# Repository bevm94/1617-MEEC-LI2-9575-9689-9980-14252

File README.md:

# 1617-MEEC-LI2-9575-9689-9980-14252
Trabalho de Laboratórios Integrados II

O presente trabalho prático visa a implementação de um sistema de reconhecimento facial que integra dois blocos principais: um baseado em PC que é responsável pelo processamento e análise de imagem e o outro é baseado em sistemas embebidos, que gere a comunicação através do protocolo de comunicação CAN dos dados analisados pelo módulo baseado em PC.
O sistema embebido foi composto pela componente de Hardware e Software. A componente de Hardware foi implementada utilizando o EAGLE onde foram implementadas duas placas: uma placa para o Master e outra para o Slave. Para a criação das PCB foram seguidas as regras disponibilizadas pelo docente e posteriormente foram criados os ficheiros GERBER essenciais para a confeção das placas. Uma vez que as PCB's não ficaram prontas em tempo útil, foi necessária a montagem em Breadboard onde foi simulado o comportamento do sistema pela utilização de LEDs e Botões.
A parte de Software que tratou do reconhecimento facial foi efetuada em Visual Studio, que também serviu de base para a criação da interface do bloco baseado em PC.

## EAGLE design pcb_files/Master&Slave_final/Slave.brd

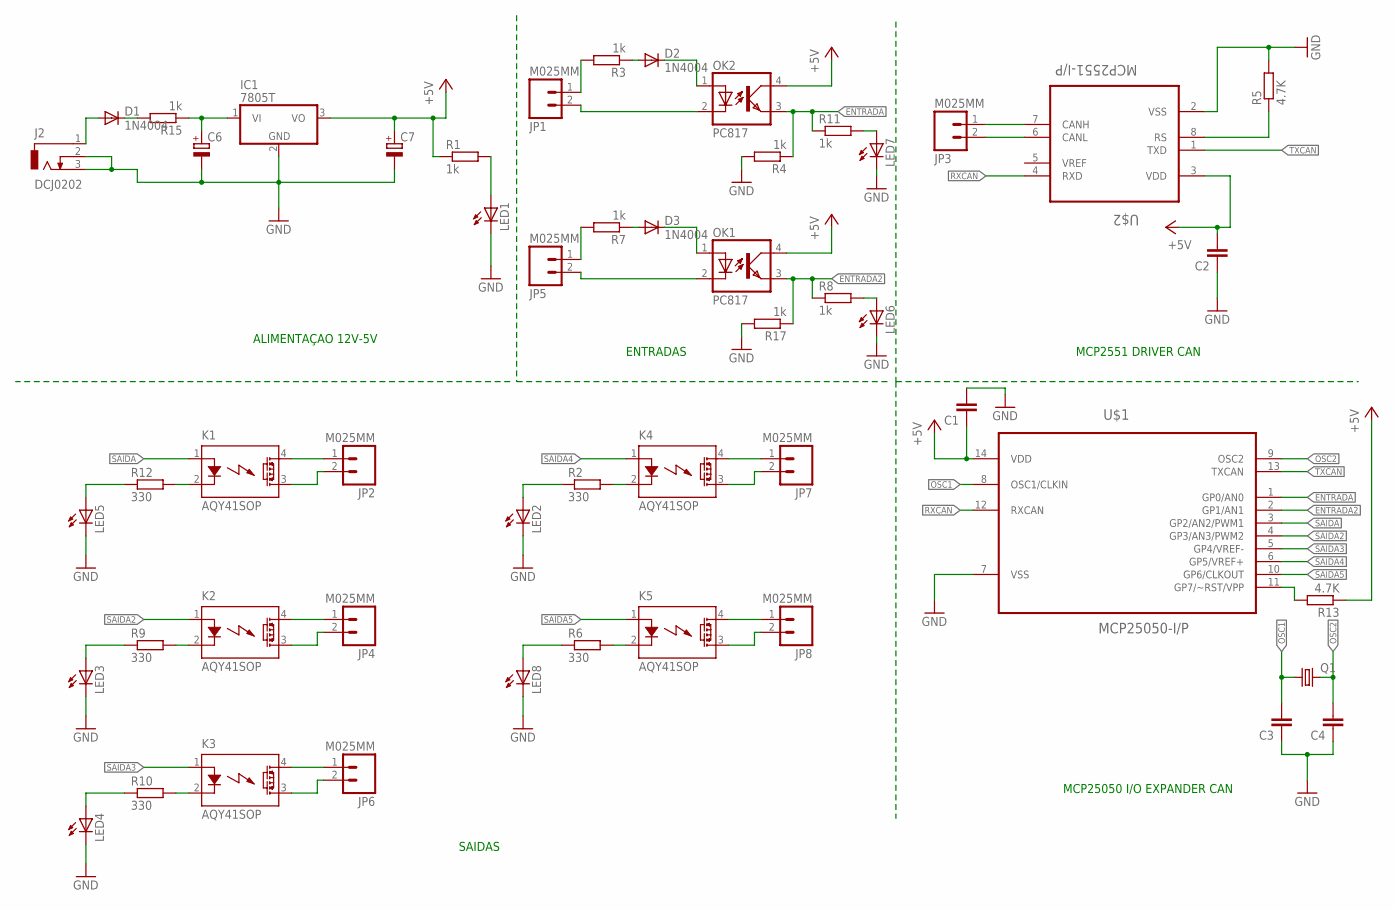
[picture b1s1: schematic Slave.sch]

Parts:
C1, C2: C-EU025-025X050; C025-025X050
C3, C4: CAP_; AXIAL-5MM
C6, C7: CPOL-EUE2.5-6; E2,5-6
D1, D2, D3: 1N4004; DO41-10
IC1: 7805T; TO220H
J2: DCJ0202
JP1, JP2, JP3, JP4, JP5, JP6, JP7, JP8: M025MM; SCREWTERMINAL-5MM-2
K1, K2, K3, K4, K5: AQY41SOP; SOP04
LED1, LED2, LED3, LED4, LED5, LED6, LED7, LED8: LED_ELD260; LED_LD260
OK1, OK2: PC817; DIL04
Q1: CRYTALHC49S; HC49/S
R1, R3, R4, R7, R8, R11, R15, R17: 1k; 0204/7
R2, R6, R9, R10, R12: 330; 0204/7
R5, R13: 4.7K; 0204/7
U$1: MCP25050-I/P; DIP254P762X432-14
U$2: MCP2551-I/P; DIP254P762X432-8

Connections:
+5V: C1.1, C2.2, C7.+, IC1.3 (VO), OK1.4 (COL), OK2.4 (COL), R1.1, R13.1, U$1.14 (VDD), U$2.3 (VDD)
ENTRADA: OK2.3 (EMIT), R4.1, R11.1, U$1.1 (GP0/AN0)
ENTRADA2: OK1.3 (EMIT), R8.1, R17.1, U$1.2 (GP1/AN1)
GND: C1.2, C2.1, C3.P$1 (1), C4.P$1 (1), C6.-, C7.-, IC1.2 (GND), J2.2, J2.3, LED1.K (C), LED2.K (C), LED3.K (C), LED4.K (C), LED5.K (C), LED6.K (C), LED7.K (C), LED8.K (C), R4.2, R5.2, R17.2, U$1.7 (VSS), U$2.2 (VSS)
unnamed: R5.1, U$2.8 (RS)
unnamed: JP2.2, K1.3 (DS2)
unnamed: JP2.1, K1.4 (DS1)
unnamed: K2.2 (K), R9.2
unnamed: JP1.1, R3.2
unnamed: LED1.A, R1.2
unnamed: R13.2, U$1.11 (GP7/~RST/VPP)
unnamed: D2.A, R3.1
unnamed: D2.C, OK2.1 (A)
unnamed: JP1.2, OK2.2 (C)
unnamed: D1.A, J2.1
unnamed: JP5.1, R7.2
unnamed: D1.C, R15.2
unnamed: D3.A, R7.1
unnamed: D3.C, OK1.1 (A)
unnamed: JP3.1, U$2.7 (CANH)
unnamed: LED3.A, R9.1
unnamed: JP4.2, K2.3 (DS2)
unnamed: JP4.1, K2.4 (DS1)
unnamed: K1.2 (K), R12.2
unnamed: LED5.A, R12.1
unnamed: K3.2 (K), R10.2
unnamed: LED4.A, R10.1
unnamed: JP6.2, K3.3 (DS2)
unnamed: JP6.1, K3.4 (DS1)
unnamed: C6.+, IC1.1 (VI), R15.1
unnamed: JP3.2, U$2.6 (CANL)
unnamed: LED6.A, R8.2
unnamed: LED7.A, R11.2
unnamed: K4.2 (K), R2.2
unnamed: JP5.2, OK1.2 (C)
unnamed: LED2.A, R2.1
unnamed: JP7.2, K4.3 (DS2)
unnamed: JP7.1, K4.4 (DS1)
unnamed: K5.2 (K), R6.2
unnamed: LED8.A, R6.1
unnamed: JP8.2, K5.3 (DS2)
unnamed: JP8.1, K5.4 (DS1)
OSC1: C3.P$2 (2), Q1.1, U$1.8 (OSC1/CLKIN)
OSC2: C4.P$2 (2), Q1.2, U$1.9 (OSC2)
RXCAN: U$1.12 (RXCAN), U$2.4 (RXD)
SAIDA: K1.1 (A), U$1.3 (GP2/AN2/PWM1)
SAIDA2: K2.1 (A), U$1.4 (GP3/AN3/PWM2)
SAIDA3: K3.1 (A), U$1.5 (GP4/VREF-)
SAIDA4: K4.1 (A), U$1.6 (GP5/VREF+)
SAIDA5: K5.1 (A), U$1.10 (GP6/CLKOUT)
TXCAN: U$1.13 (TXCAN), U$2.1 (TXD)

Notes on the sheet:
MCP2551 DRIVER CAN
MCP25050 I/O EXPANDER CAN
ALIMENTAÇAO 12V-5V
SAIDAS
ENTRADAS

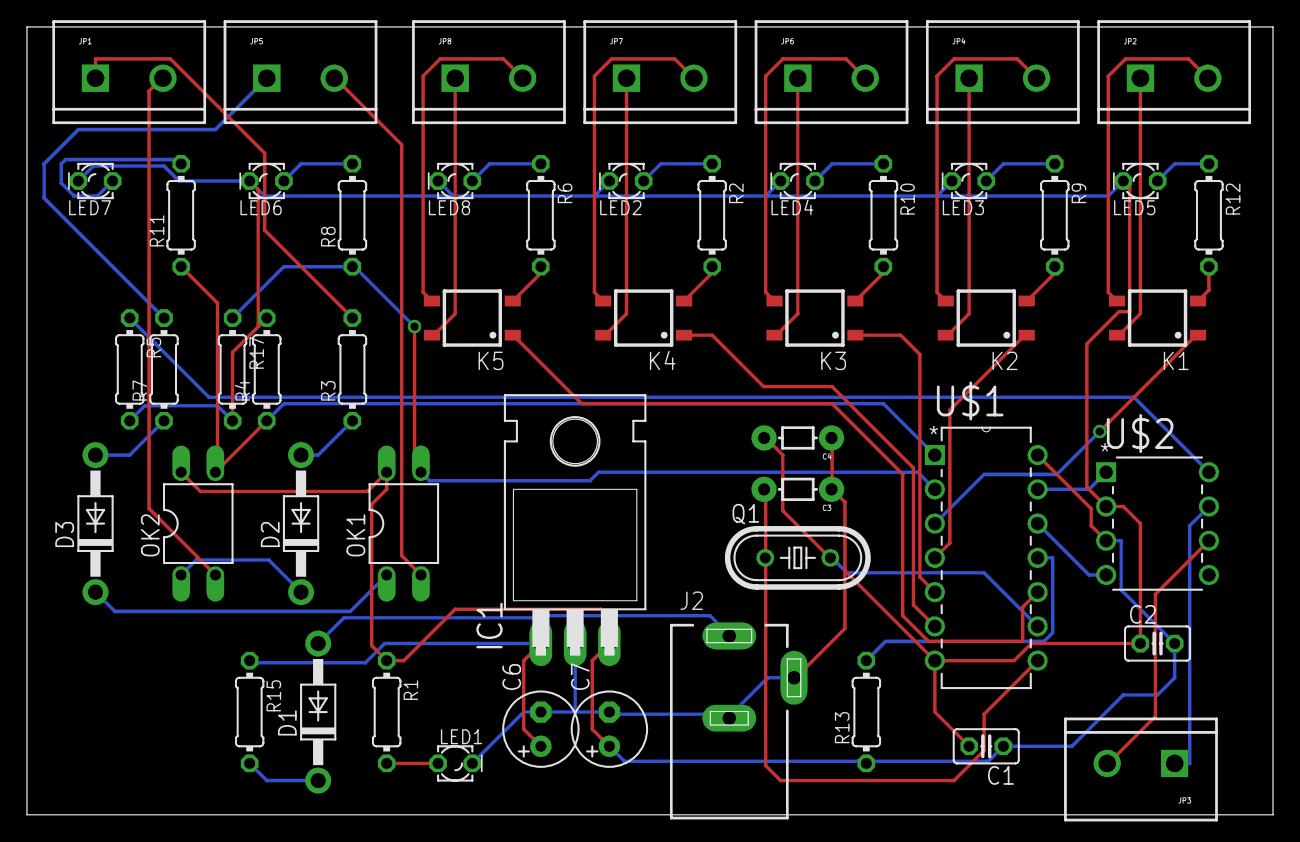
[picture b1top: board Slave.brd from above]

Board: 2 copper layers, 92.4 x 58.4 mm, 52 parts (0 on the bottom side), 51 nets.

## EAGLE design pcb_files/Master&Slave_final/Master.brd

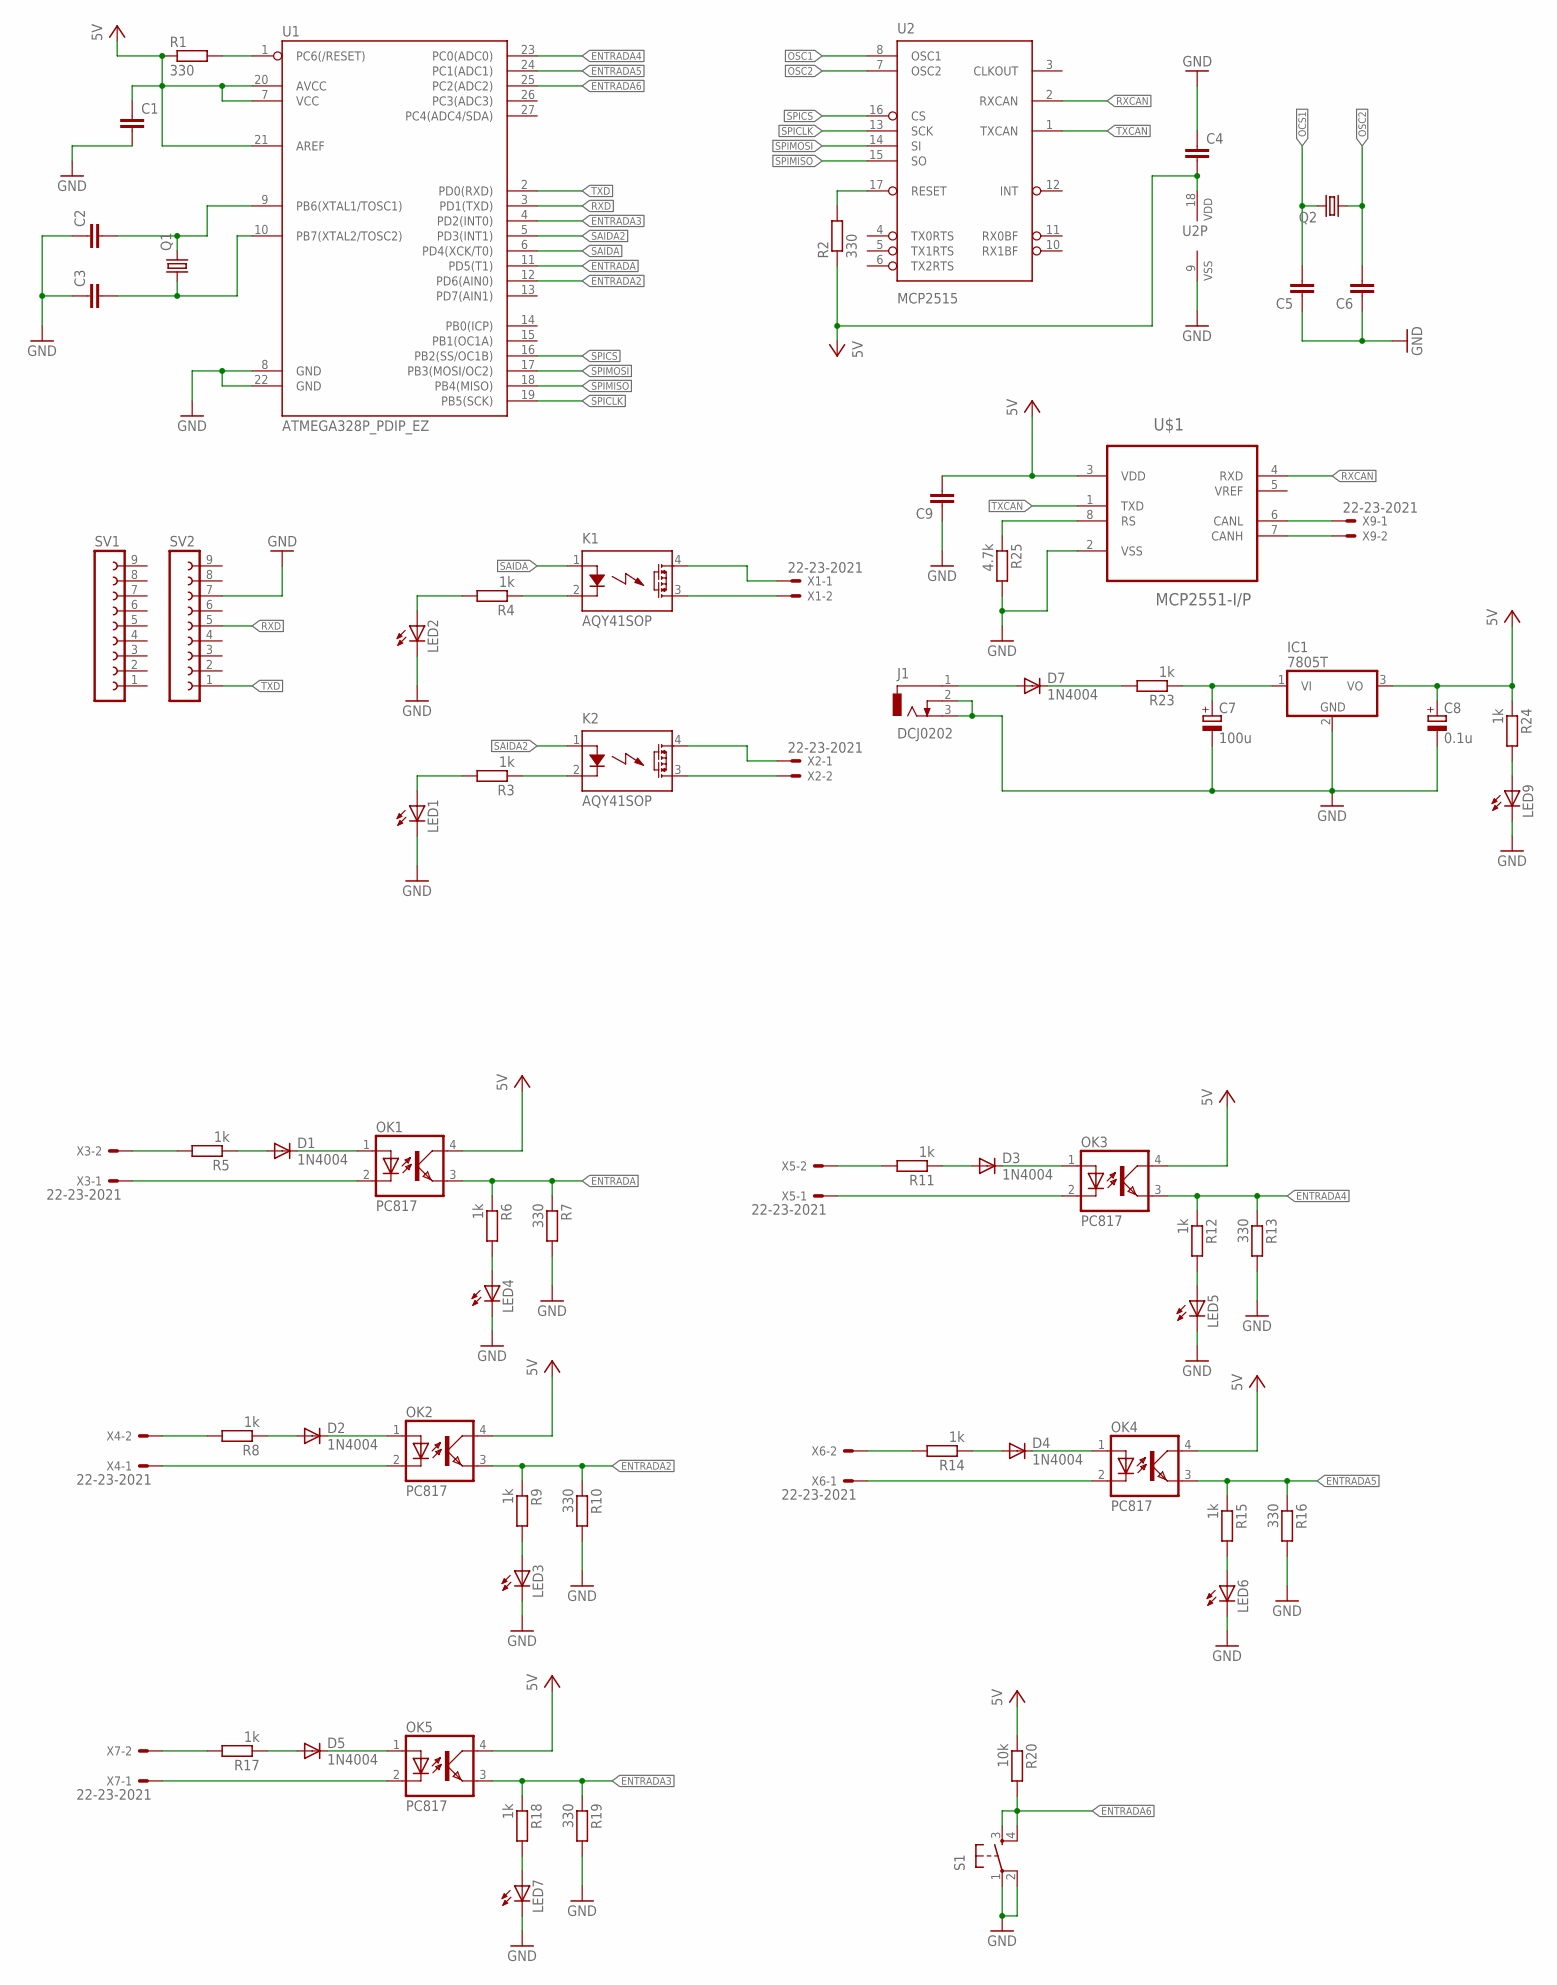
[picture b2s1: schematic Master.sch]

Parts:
C1, C2, C3, C4, C5, C6, C9: C2,5-3; C2.5-3
C7: 100u; E2,5-6
C8: 0.1u; E2,5-6
D1, D2, D3, D4, D5, D7: 1N4004; DO41-10
IC1: 7805T; TO220H
J1: DCJ0202
K1, K2: AQY41SOP; SOP04
LED1, LED2, LED3, LED4, LED5, LED6, LED7, LED9: LED_ELD260; LED_LD260
OK1, OK2, OK3, OK4, OK5: PC817; DIL04
Q1, Q2: CRYSTALHC49U70; HC49U70
R1, R2, R7, R10, R13, R16, R19: 330; 0204/5
R3, R4, R5, R6, R8, R9, R11, R12, R14, R15, R17, R18, R23, R24: 1k; 0204/5
R20: 10k; 0204/5
R25: 4.7k; 0204/5
S1: TAC_SWITCHPTH; TACTILE-PTH
SV1, SV2: FE09-1; FE09
U1: ATMEGA328P_PDIP_EZ; DIP28-SIMON-KIT
U2: MCP2515; DIP18
U$1: MCP2551-I/P; DIP254P762X432-8
X1, X2, X3, X4, X5, X6, X7, X9: 22-23-2021

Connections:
ENTRADA: OK1.3 (EMIT), R6.1, R7.1, U1.11 (PD5(T1))
ENTRADA2: OK2.3 (EMIT), R9.1, R10.1, U1.12 (PD6(AIN0))
ENTRADA3: OK5.3 (EMIT), R18.1, R19.1, U1.4 (PD2(INT0))
ENTRADA4: OK3.3 (EMIT), R12.1, R13.1, U1.23 (PC0(ADC0))
ENTRADA5: OK4.3 (EMIT), R15.1, R16.1, U1.24 (PC1(ADC1))
ENTRADA6: R20.2, S1.3, S1.4, U1.25 (PC2(ADC2))
GND: C1.2, C2.1, C3.1, C4.1, C5.1, C6.1, C7.-, C8.-, C9.1, IC1.2 (GND), J1.2, J1.3, LED1.K (C), LED2.K (C), LED3.K (C), LED4.K (C), LED5.K (C), LED6.K (C), LED7.K (C), LED9.K (C), R7.2, R10.2, R13.2, R16.2, R19.2, R25.2, S1.1, S1.2, SV2.7, U1.8 (GND), U1.22 (GND), U2.9 (VSS), U$1.2 (VSS)
unnamed: R1.2, U1.1 (PC6(/RESET))
unnamed: C2.2, Q1.2, U1.9 (PB6(XTAL1/TOSC1))
unnamed: C3.2, Q1.1, U1.10 (PB7(XTAL2/TOSC2))
unnamed: R2.2, U2.17 (RESET)
unnamed: LED1.A, R3.2
unnamed: K2.2 (K), R3.1
unnamed: K1.2 (K), R4.1
unnamed: LED2.A, R4.2
unnamed: K1.3 (DS2), X1.2
unnamed: K1.4 (DS1), X1.1
unnamed: K2.4 (DS1), X2.1
unnamed: K2.3 (DS2), X2.2
unnamed: R5.2, X3.2
unnamed: D1.A, R5.1
unnamed: D1.C, OK1.1 (A)
unnamed: OK1.2 (C), X3.1
unnamed: R8.2, X4.2
unnamed: LED4.A, R6.2
unnamed: D2.A, R8.1
unnamed: D2.C, OK2.1 (A)
unnamed: OK2.2 (C), X4.1
unnamed: LED3.A, R9.2
unnamed: R11.2, X5.2
unnamed: D3.A, R11.1
unnamed: D3.C, OK3.1 (A)
unnamed: OK3.2 (C), X5.1
unnamed: LED5.A, R12.2
unnamed: R14.2, X6.2
unnamed: D4.A, R14.1
unnamed: D4.C, OK4.1 (A)
unnamed: OK4.2 (C), X6.1
unnamed: LED6.A, R15.2
unnamed: R17.2, X7.2
unnamed: D5.A, R17.1
unnamed: D5.C, OK5.1 (A)
unnamed: OK5.2 (C), X7.1
unnamed: LED7.A, R18.2
unnamed: D7.A, J1.1
unnamed: D7.C, R23.2
unnamed: C7.+, IC1.1 (VI), R23.1
unnamed: U$1.6 (CANL), X9.1
unnamed: U$1.7 (CANH), X9.2
unnamed: LED9.A, R24.2
unnamed: R25.1, U$1.8 (RS)
OCS1: C5.2, Q2.2
OSC1: U2.8 (OSC1)
OSC2: C6.2, Q2.1, U2.7 (OSC2)
RXCAN: U2.2 (RXCAN), U$1.4 (RXD)
RXD: SV2.5, U1.3 (PD1(TXD))
SAIDA: K1.1 (A), U1.6 (PD4(XCK/T0))
SAIDA2: K2.1 (A), U1.5 (PD3(INT1))
SPICLK: U1.19 (PB5(SCK)), U2.13 (SCK)
SPICS: U1.16 (PB2(SS/OC1B)), U2.16 (CS)
SPIMISO: U1.18 (PB4(MISO)), U2.15 (SO)
SPIMOSI: U1.17 (PB3(MOSI/OC2)), U2.14 (SI)
TXCAN: U2.1 (TXCAN), U$1.1 (TXD)
TXD: SV2.1, U1.2 (PD0(RXD))
VCC: C1.1, C4.2, C8.+, C9.2, IC1.3 (VO), OK1.4 (COL), OK2.4 (COL), OK3.4 (COL), OK4.4 (COL), OK5.4 (COL), R1.1, R2.1, R20.1, R24.1, U1.7 (VCC), U1.20 (AVCC), U1.21 (AREF), U2.18 (VDD), U$1.3 (VDD)

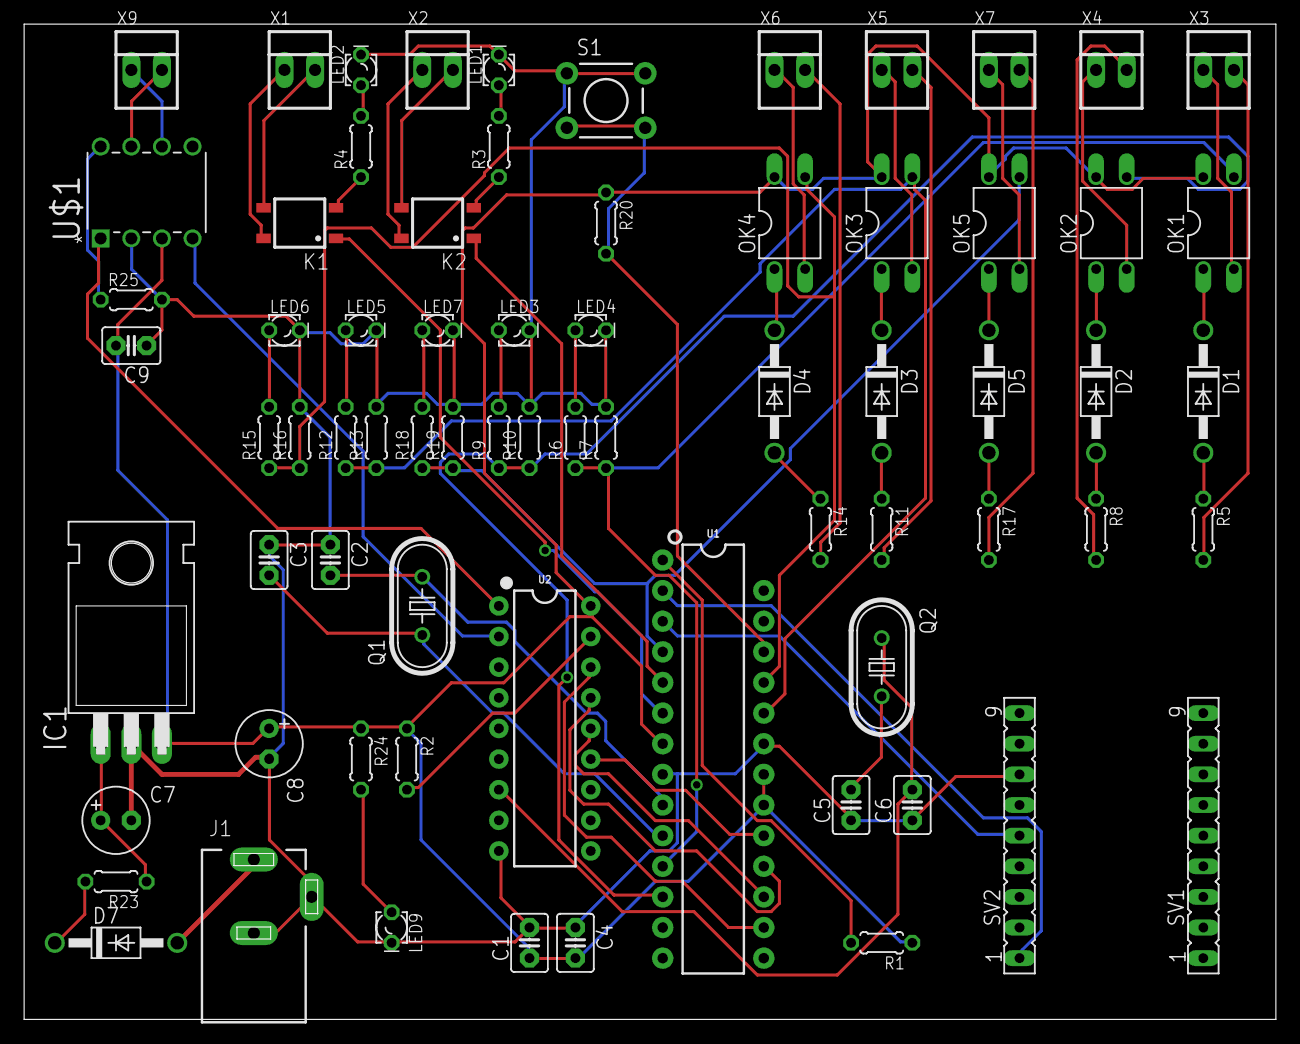
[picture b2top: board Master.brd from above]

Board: 2 copper layers, 103.8 x 82.5 mm, 71 parts (0 on the bottom side), 64 nets.

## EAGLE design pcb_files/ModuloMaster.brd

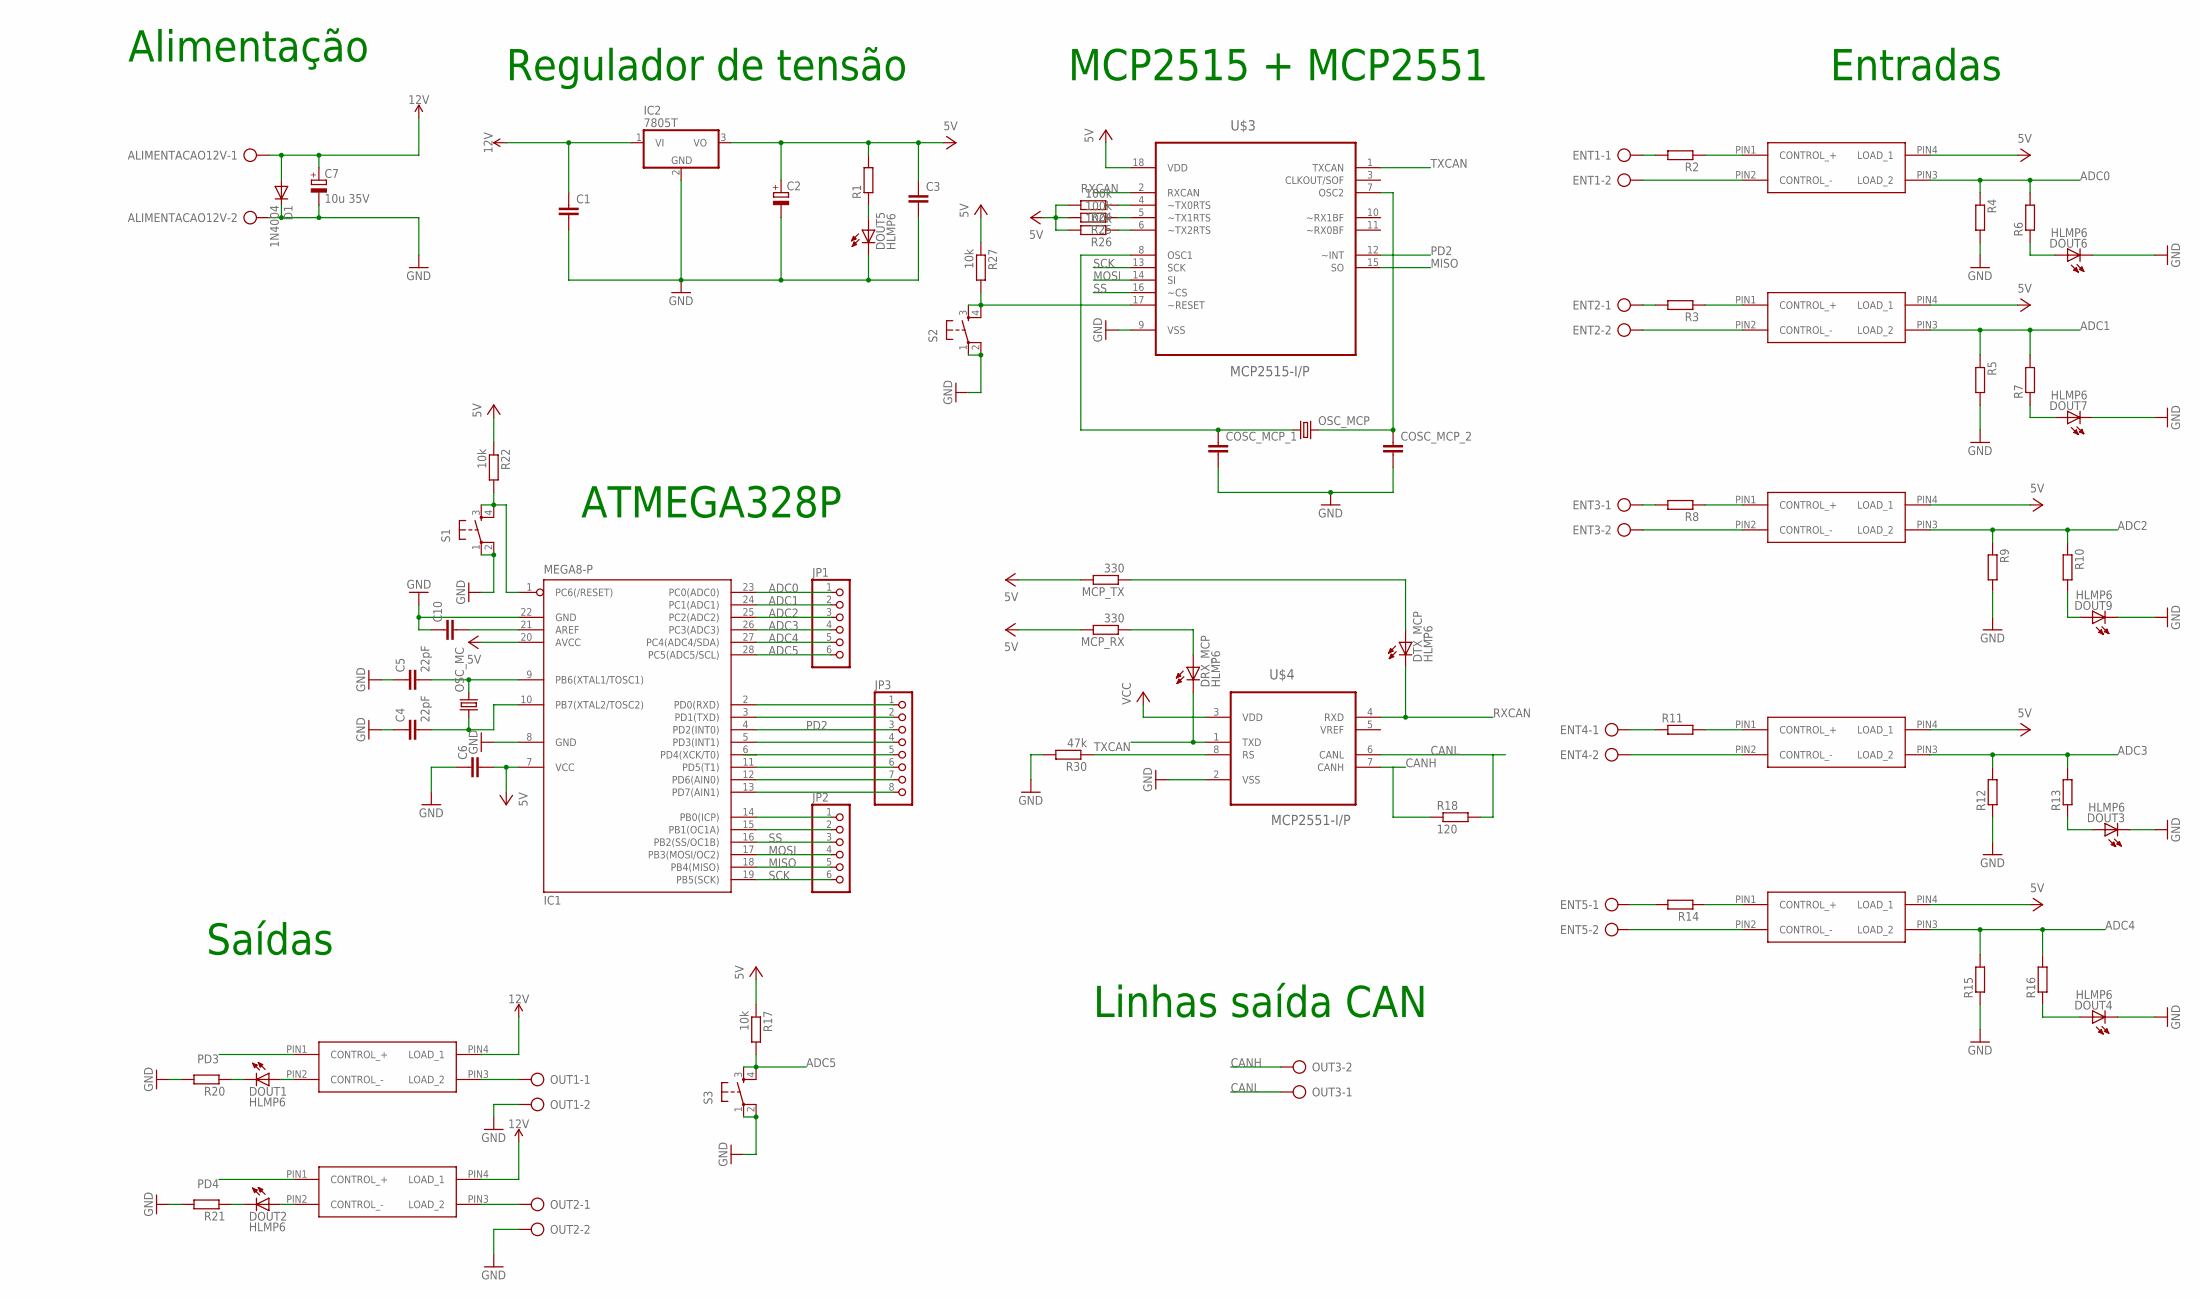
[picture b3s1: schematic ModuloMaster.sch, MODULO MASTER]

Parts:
ALIMENTACAO12V: AK300/2
C1, C3: C-EU025-025X050; C025-025X050
C2: CPOL-EUSANYO_C6; SANYO-OSCON_C6
C4, C5: 22pF; AXIAL-5MM
C6, C10: CAP_; AXIAL-5MM
C7: 10u 35V; SANYO-OSCON_C6
COSC_MCP_1, COSC_MCP_2: CAP_; AXIAL-5MM
D1: 1N4004; DO41-10
DOUT1, DOUT2, DOUT3, DOUT4, DOUT5, DOUT6, DOUT7, DOUT9: HLMP6
DRX_MCP: HLMP6
DTX_MCP: HLMP6
ENT1, ENT2, ENT3, ENT4, ENT5: AK300/2
IC1: MEGA8-P; DIL28-3
IC2: 7805T; TO220H
JP1, JP2: PINHD-1X6; 1X06
JP3: PINHD-1X8; 1X08
MCP_RX: 330; 0204/7
MCP_TX: 330; 0204/7
OSC_MC: CRYSTALHC49S; HC49/S
OSC_MCP: CRYSTALHC49S; HC49/S
OUT1, OUT2, OUT3: AK300/2
R1, R2, R3, R4, R5, R6, R7, R8, R9, R10, R11, R12, R13, R14, R15, R16, R20, R21: R-EU_0204/7; 0204/7
R17, R22, R27: 10k; 0204/7
R18: 120; 0204/7
R24, R25, R26: 100k; 0204/7
R30: 47k; 0204/7
S1, S2, S3: TAC_SWITCHPTH; TACTILE-PTH
U$1, U$2, U$5, U$6, U$7, U$8, U$9: OPTO-RELAY-CPC1017N; SOP-4
U$3: MCP2515-I/P; DIP254P762X432-18
U$4: MCP2551-I/P; DIP254P762X432-8

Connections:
5V: C2.+, C3.1, IC2.3 (VO), R1.2
ADC0: IC1.23 (PC0(ADC0)), JP1.1, R4.1, R6.2, U$5.PIN3 (LOAD_2)
ADC1: IC1.24 (PC1(ADC1)), JP1.2, R5.1, R7.2, U$6.PIN3 (LOAD_2)
ADC2: IC1.25 (PC2(ADC2)), JP1.3, R9.1, R10.1, U$7.PIN3 (LOAD_2)
ADC3: IC1.26 (PC3(ADC3)), JP1.4, R12.2, R13.2, U$8.PIN3 (LOAD_2)
ADC4: IC1.27 (PC4(ADC4/SDA)), JP1.5, R15.2, R16.2, U$9.PIN3 (LOAD_2)
ADC5: IC1.28 (PC5(ADC5/SCL)), JP1.6, R17.2, S3.3, S3.4
CANH: OUT3.2, R18.1, U$4.7 (CANH)
CANL: OUT3.1, R18.2, U$4.6 (CANL)
GND: ALIMENTACAO12V.2, C1.2, C2.-, C3.2, C4.P$1 (1), C5.P$1 (1), C6.P$1 (1), C7.-, C10.P$1 (1), COSC_MCP_1.P$2 (2), COSC_MCP_2.P$2 (2), D1.C, DOUT3.K, DOUT4.K, DOUT5.K, DOUT6.K, DOUT7.K, DOUT9.K, IC1.8 (GND), IC1.22 (GND), IC2.2 (GND), OUT1.2, OUT2.2, R4.2, R5.2, R9.2, R12.1, R15.1, R20.2, R21.2, R30.2, S1.1, S1.2, S2.1, S2.2, S3.1, S3.2, U$3.9 (VSS), U$4.2 (VSS)
MISO: IC1.18 (PB4(MISO)), JP2.5, U$3.15 (SO)
MOSI: IC1.17 (PB3(MOSI/OC2)), JP2.4, U$3.14 (SI)
unnamed: DOUT2.A, U$2.PIN2 (CONTROL_-)
unnamed: DOUT1.A, U$1.PIN2 (CONTROL_-)
unnamed: C4.P$2 (2), IC1.10 (PB7(XTAL2/TOSC2)), OSC_MC.1
unnamed: C5.P$2 (2), IC1.9 (PB6(XTAL1/TOSC1)), OSC_MC.2
unnamed: ENT4.1, R11.1
unnamed: DRX_MCP.A, MCP_RX.1
unnamed: DTX_MCP.A, MCP_TX.1
unnamed: R11.2, U$8.PIN1 (CONTROL_+)
unnamed: C10.P$2 (2), IC1.21 (AREF)
unnamed: ENT1.1, R2.2
unnamed: R2.1, U$5.PIN1 (CONTROL_+)
unnamed: ENT4.2, U$8.PIN2 (CONTROL_-)
unnamed: COSC_MCP_1.P$1 (1), OSC_MCP.1, U$3.8 (OSC1)
unnamed: COSC_MCP_2.P$1 (1), OSC_MCP.2, U$3.7 (OSC2)
unnamed: ENT5.1, R14.2
unnamed: R14.1, U$9.PIN1 (CONTROL_+)
unnamed: ENT5.2, U$9.PIN2 (CONTROL_-)
unnamed: ENT1.2, U$5.PIN2 (CONTROL_-)
unnamed: ENT2.1, R3.2
unnamed: OUT1.1, U$1.PIN3 (LOAD_2)
unnamed: IC1.1 (PC6(/RESET)), R22.2, S1.3, S1.4
unnamed: DOUT1.K, R20.1
unnamed: OUT2.1, U$2.PIN3 (LOAD_2)
unnamed: DOUT2.K, R21.1
unnamed: R30.1, U$4.8 (RS)
unnamed: R25.1, U$3.5 (~TX1RTS)
unnamed: R24.1, U$3.4 (~TX0RTS)
unnamed: R26.1, U$3.6 (~TX2RTS)
unnamed: ENT2.2, U$6.PIN2 (CONTROL_-)
unnamed: R3.1, U$6.PIN1 (CONTROL_+)
unnamed: DOUT5.A, R1.1
unnamed: DOUT6.A, R6.1
unnamed: DOUT7.A, R7.1
unnamed: R27.2, S2.3, S2.4, U$3.17 (~RESET)
unnamed: DOUT3.A, R13.1
unnamed: ENT3.1, R8.2
unnamed: R8.1, U$7.PIN1 (CONTROL_+)
unnamed: ENT3.2, U$7.PIN2 (CONTROL_-)
unnamed: DOUT9.A, R10.2
unnamed: DOUT4.A, R16.1
unnamed: IC1.14 (PB0(ICP)), JP2.1
unnamed: IC1.15 (PB1(OC1A)), JP2.2
unnamed: IC1.2 (PD0(RXD)), JP3.1
unnamed: IC1.3 (PD1(TXD)), JP3.2
unnamed: IC1.13 (PD7(AIN1)), JP3.8
unnamed: IC1.12 (PD6(AIN0)), JP3.7
unnamed: IC1.11 (PD5(T1)), JP3.6
PD2: IC1.4 (PD2(INT0)), JP3.3, U$3.12 (~INT)
PD3: IC1.5 (PD3(INT1)), JP3.4, U$1.PIN1 (CONTROL_+)
PD4: IC1.6 (PD4(XCK/T0)), JP3.5, U$2.PIN1 (CONTROL_+)
RXCAN: DTX_MCP.K, U$3.2 (RXCAN), U$4.4 (RXD)
SCK: IC1.19 (PB5(SCK)), JP2.6, U$3.13 (SCK)
SS: IC1.16 (PB2(SS/OC1B)), JP2.3, U$3.16 (~CS)
TXCAN: DRX_MCP.K, U$3.1 (TXCAN), U$4.1 (TXD)
VCC: C6.P$2 (2), IC1.7 (VCC), IC1.20 (AVCC), MCP_RX.2, MCP_TX.2, R17.1, R22.1, R24.2, R25.2, R26.2, R27.1, U$3.18 (VDD), U$4.3 (VDD), U$5.PIN4 (LOAD_1), U$6.PIN4 (LOAD_1), U$7.PIN4 (LOAD_1), U$8.PIN4 (LOAD_1), U$9.PIN4 (LOAD_1)
VDD: ALIMENTACAO12V.1, C1.1, C7.+, D1.A, IC2.1 (VI), U$1.PIN4 (LOAD_1), U$2.PIN4 (LOAD_1)

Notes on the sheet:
Entradas
Saídas
Linhas saída CAN
Regulador de tensão
Alimentação
MCP2515 + MCP2551
ATMEGA328P

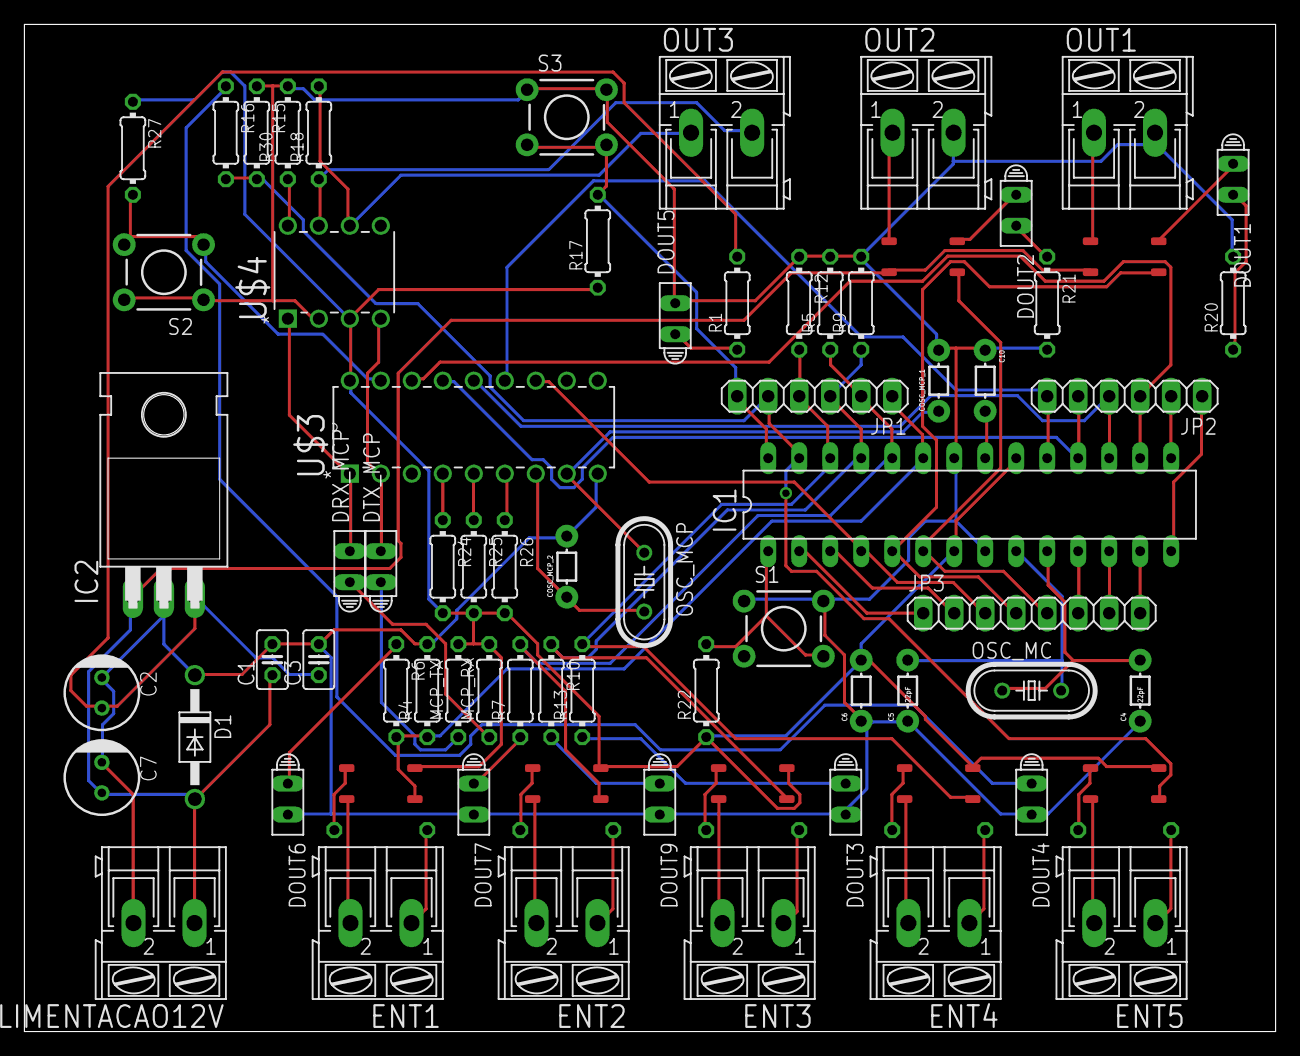
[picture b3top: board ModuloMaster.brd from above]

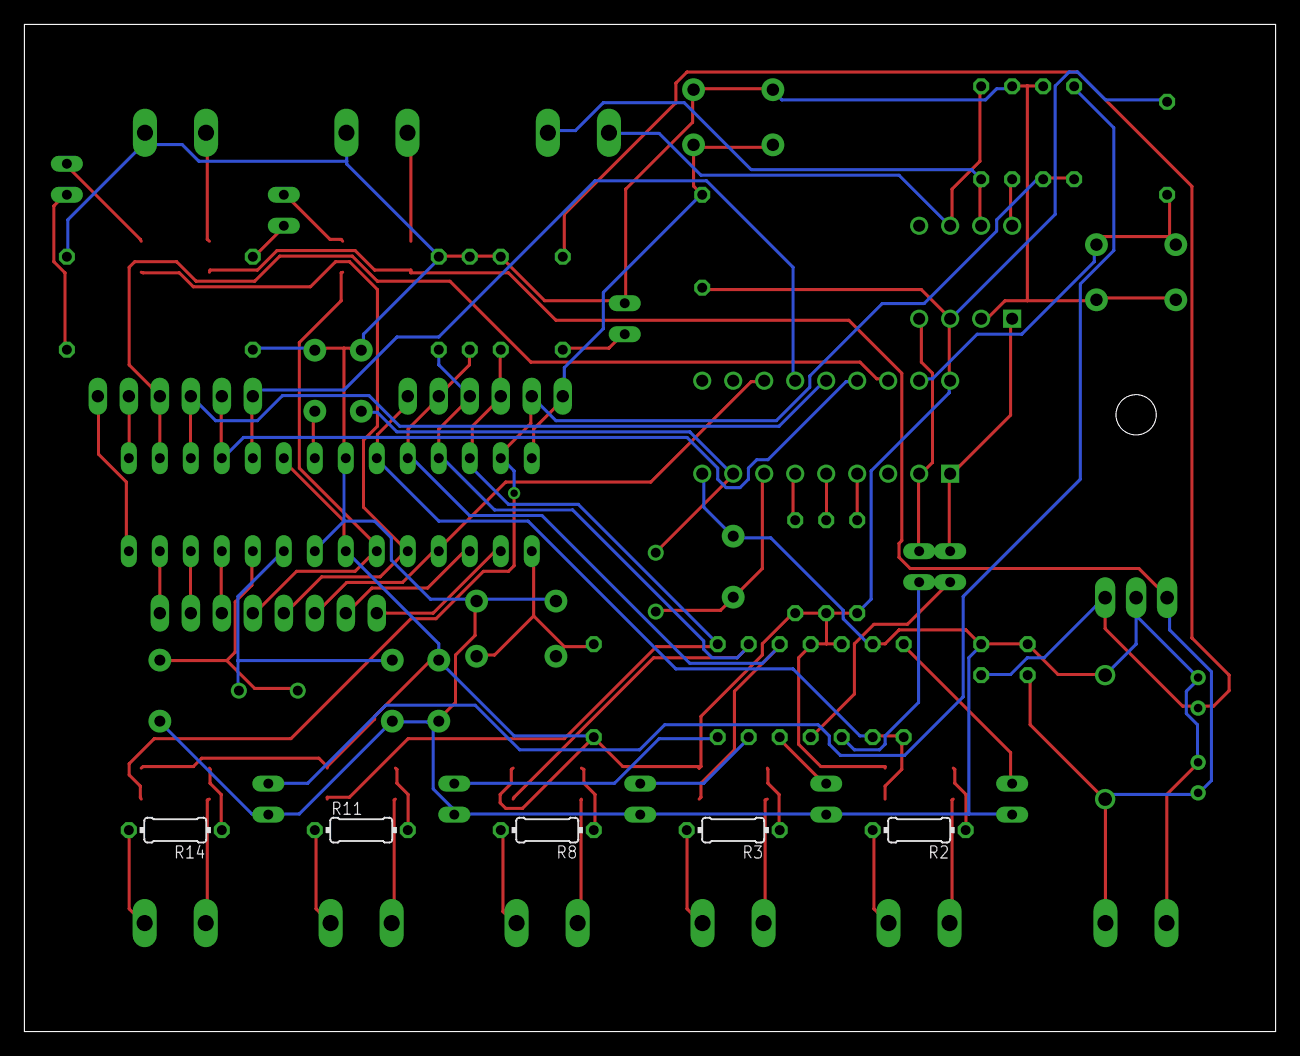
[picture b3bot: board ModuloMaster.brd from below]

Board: 2 copper layers, 102.5 x 82.5 mm, 77 parts (5 on the bottom side), 68 nets.

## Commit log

2017-04-26 Primeira organização do repositório
    Contém uma primeira organização dos ficheiros do repositório.
    Convém guardar aqui todas as alterações dos programas que usamos
2017-04-30 Resolução do 1º trabalho preparatório
    Resolução do 1º trabalho preparatório. Neste trabalho preparatório foi
    explorado o funcionamento do integrado MCP2515 bem como explorados todo
    um conjunto de registos que irão ser necessários à elaboração do
    projecto.
2017-05-02 Resolução do 2º trabalho preparatório
    Resolução do 2º trabalho preparatório. Neste trabalho preparatório foi
    explorado o príncipio e base de funcionamento do integrado MCP25050.
2017-05-09 Adição do projeto base de C#
    Adição do projeto base de c#
2017-05-09 Adição do esquemático da pcb
    Esquemático da PCB
2017-05-09 Alteração Serial Configuration
    Alteração na configuração da porta série
2017-05-09 Alteração de botão no Main Design
    Alteração de botão no Main Design
2017-05-09 Nenhuma alteração
    Não houve nenhuma alteração efetuada
2017-05-09 Nenhuma alteração
    Nenhuma alteração
2017-05-10 Branch Teste
    Teste de branch
2017-05-10 Mais um teste
2017-05-10 Mais outro teste
2017-05-10 Porta série a funcionar
    Porta série funcional
2017-05-10 Implementação da porta série
    Implementação da porta série na aplicação. Teste de ligação com Arduíno.
2017-05-15 Configuração da Porta série adicionada
    Realizou-se a adição da configuração da porta série na API.
2017-05-17 Alteração da base de dados
    Alteração da base de dados da API e alteração de template xml utilizado
    para detetar faces
2017-05-24 Esquemático Módulo Master
    Primeira versão do PCB para módulo master.
2017-05-30 Modulo expansão
    *faltam ligações
2017-07-20 Fix some issues in Master and Slave module
    Fix some issues.
    Frist broad for Master module.
2017-07-22 Adição de edição da base de dados Adição do treino de faces
2017-07-22 Final sch and brd to master and slave modules
    Conclusão da conceção da PCB do módulo master e módulo slave.
2017-07-22 Resume
    Inserção de um pequeno resumo do trabalho desenvolvido.
2017-07-22 Fix resume
    Fix resume
2017-07-23 Relatório
    Primeiro template de relatório.
    Definição de estrutura para elaboração do relatório final.
2017-07-23 Nova versão relatório
    Fix some issues.
2017-07-26 Update de funcionalidades do software
    Treino de faces numa janela independente
    Visualização das faces e nomes guardados
    Precisa - se de:
    - acabar a comunicação
    - apagar faces selecionadas
    - testar a comunicação
2017-07-26 Update do relatório
    Relatório
2017-07-27 Relatório versão final
    Adição da versão final do relatório e versão pdf.
    Já foi enviado a versão final em pdf.

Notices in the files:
parts and their libraries:
SparkFun-Retired: Licensing: Creative Commons ShareAlike 4.0 International - https://creativecommons.org/licenses/by-sa/4.0
